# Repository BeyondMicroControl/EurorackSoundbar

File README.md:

# Eurorack Soundbar
Goal: A table with fitting speaker & synth electronics for a MIDI keyboard.

# Piano enclosures deserve better design
It all started with buying an all-in-one furnished hammer-action piano with built-in synth and speakers, but ending 25 years later with a shell containing a terribly old synth and procrastinating MIDI interface.  That said, while build quality on all parts of the piano gracefull survived decades of playing, electronics inside turned out to be fashion-sensitive. As a matter of fact, furniture built-in synths sooner or later all become **OBSOLETE**. I long thought about flinging out the guts out of my good old Clavinova from Yamaha built around a synth chip from 1991 (YMW258-F), but selling my old piano in its original state and figure out a more future-proof enclosure sounded like a better idea, as I really wanted an enclosure allowing more flexibility.  So, here's the plan: 
* Buy a multi-sensor MIDI keyboard - I fell for a KAWAI VPC1, but any model will do.
* Design a slim, good-looking table on wheels carrying about 30Kg=66lbs of keyboard and another 20Kg=44lbs of soundbar.
* Design a soundbar including a standardised built-in rack space for replacable electronics : **A Eurorack Soundbar as it were!**

# Eurorack Soundbar Requirements
## Furniture
1.1) Elegant & aesthetically matching the MIDI keyboard<br>
1.2) Providing table surface fitting Piano Keyboard + Soundbar.<br>
1.3) Sturdy enough to bear stress and strain caused by ~50Kg=110lbs of weight<br>
1.4) Providing maximum leg space horizontally and vertically.<br>
1.5) Height-adjustable to some extent.<br>
1.6) Piano-black glossy paint finish.<br>

## Speaker enclosure - passive part
2.1) Perfectly fitting keyboard width, and height aligned with the top of the speaker grills.<br>
2.2) Best compromise between good bass production and small enclosure volume.<br>
2.3) Rich sound spectrum and spatial perception ideal for instrument sound reproduction.<br>
2.4) Optional built-in passive filter and accessble attenuators whenever necessary.<br>
2.5) Die-cast, anti-reflection and airleak-proof speaker enclosure.<br>
2.6) Vibration isolation between table & enclosure.<br>
2.7) Does not vibrate or glide off the table.<br>
2.8) Re-openable, allowing replacement of speakers provided with inside fixture.<br>
2.9) All speaker leads and filter leads come straight out of the pressure cabinet. (No electrical circuits inside)<br>
2.10) One common connector (male part) providing electrically separate access to all enclosed speakers and filters.<br>
2.11) Nicely fitting speaker cover frame wrapped in speaker cover fabric, with magnetic attachment<br>
2.12) Speakers pointing upwards, providing a fairly unobstructed sound path<br>

## Electronics enclosure - active part
3.1) One common connector (female part, heading towards the amplifier) with configurable dispatching jumpers.<br>
3.2) Standard Eurorack frame housing 3U 84HP (decisive for speaker enclosure depth).<br>
3.3) Eurorack power source (Low noise 15-35V source for Amps, 5V & 3V3 regulated source for MCU's and controllers), optionally with a 1-button on/off and power-on sequence.<br>
3.4) A good compromise on the divide between Eurorack enclosure height (located between bottom plate and face plate) and speaker enclosure duct height (located under the Eurorack bottom plate).<br>
3.6) Mains inlet connector with fast fuse and manual switch.<br>
3.5) At least 3 essential Eurorack modules<br>
   - Amp (2 x 30-80W)
   - Piano connector face plate (USB-midi, MIDI-in/out)
   - Synth module (MIDI-in to audio)

3.6) Optional Eurorack modules - just brainstorming<br>
   - Battery module providing mobile power
   - Additional experimental synths (without patch cable clutter)
   - MIDI merger/splitter module
   - MIDI controller module (encoders, buttons, sliders, tone wheels, LEDs, touchscreens...)
   - MIDI sequencer / tempo

# Getting sketchy with it

This is the initial sketch, for what it's worth, outlining all elements including the Piano; we'll come back later on the exact measures and additional features; obviously depending on the MIDI keyboard outer dimensions one has purchased.  

This is our first step, planning how this soundbar will fit best fit behind your MIDI keyboard, the outer dimensions of the table, how your knees will ideally fit under that table, and many other practical considerations.

# Hardware

<a href="https://beyondmicrocontrol.github.io/AsciiCAD/index.html?d=eNrdm8tu20YUhvd+ilnGCFhrqKuXjuykaiwJlWTBgCADXXhbA21gpF3FWnURBBRAOUQgo6mq9IIYSBduFwXaRR+gD8En6eFlyBnORSQtiZMKY1miyNGZ75w55+eIrD6vonbrsIVanb3uyQD14Omoh7b3eNI5RK59xbYP3Jb0bSPH7qCiHw+rQ+D0wm+35MWEvEjTbtm3mY5NdCI9tnhOwQNMDJ+4rYLt4bbgD4ZxBRt24dWTL56dJ0bkzmx3ZnHtNdefeD/5AbKBqPpJ14k7/SkxZtd+KQ+ErHFhidk1hzurjXdnU3jeg90v3Nl7plPkvvoraoTFFI1qHVxujMMj04z++jvYd/QZxmMY9qAD30NNqhEu/fP747Eqisjjggsg72hyuGvbFL2IIaEBs9fDMWXJh63v2RR+Mnt/Af/2IjauPYf3I9Ms/fvrmKCBzxYPOs1dhIbNpjv7PsVsl3tPFHPTs7OzcI/rv+F5wHqHb7+49ttc+URtGuOAB7QD5pIvv6Wovn4himzeN9gkzpnE/rm+C170yNAdEnN0tFphpnn1Z9QS1s0Ww8cPvcOGR+ApNg8lIlyUl1Bk2ITM2x4bw6uz4FztpQvqjcPa4b0a4U61gevjYIbPk/Sgfu+wNtqUjYIJfkd5gXjr+g+qZyeaC4DO8NF1JUEe9zKq1KkZoiZp06FNu3g70W3R1YlkoAfiVP+zIG3SgxOmXoME9OXlJR3N7CzmM43fFbi7giuNwN0kzYCTfQ/cckQc8QSYqFxgi1Mgm4/kqTnqHfAw6Tmcn56iDEclQLVDCkLJKwj2IA7UUR82JeqQg4TmUh/P3ijr/I1nJAylMk4kLXVukuRn5bfdsEAUOSHpm5AmVNcTjI7rjeOxlN4qE6Q23qTNV7yZ4lDKrskU47fjbN0NNw5bJOk4PIXNakJ3+jYNh9XyKqpmMNkhvGtjf4okZJWazaqoEzqYipatKkAFrWja12gdGEU+YwMUE1JLblOn9ck9zqrW0mgDLN3UZmDWUhLHK/QmKfMJcxMVR1Ij7BSxu8y4XRbOcTmeaKAo1blDoiqDg+yQNYpZM91KWE+Zb/gtMPik/4hY/oFTAxJmegjJ5Up8K6TkUp1cJpJaLyEqLX8CijpIPyE0tfijKvGquS4SCzSv0eD8/Muvv0GVT0pjNa+oNJi8IjQ1UoSWgGgaPbhCkaXhedBro+bFV8/OnxvtOqqVSu1Pv1XF35Y1ovyEI7VKSxlVGWbhpjXiD+k4ZFaJ9bEk4we9v1wdrLNFeA4mewxbHSoROxroRQG5KC3UMynGZdQxzD4OVxJU7xQj1OydmnCQURL9OsJVLIcqlRrqO3EMrkvhscl3ooY78OEOAriYg1seliXD9aXF9J1WGk7CdQ0qjpneEwTDWPjbuycDnxw8mWUDtZvHT7EXq0DyYB/MvtBVr6lQrVWx8SZZAo7HPSBnIqMMHE0jtKfpB+dBI+JYvGKTYluXZvNqlr+2EZfWJKtHPipkVIAVNvy3GPVO+54GqUuCwYoVXJlXcGUtFJwlobs2/cYh5dm2Ot50RkYV2JZIHA4CtjXlRGNpb1vfxX8Jt10hhHe3vsJCv75jNYwwh2KQQkYNTN0H5v3mManyB1Vv7jOD3opuXIj5CqcEEDaLInyn3IEXUmZA+wBo14F2w6N9eBDRrohpF6Q4lSkIqJeLoi74scqW6yvTyyq+sjIawLweMMeQVSoe83KKrGLpLGclpzuRmyqFu8lSyTfcBMfsg2NqQerxSqnvGJMDY7F1RCPpqzjtBA9UC/QAU9TZWT1btD/v91Cz74/PwCWEq6Tk9k7Lng8w5QOLl2F6imupQ8AVtW26Yglnb4xFURh5E6Dd7bdCiQ3wMcKVWO/48EvU2CdytaaFMpdwB+J1j7h/aWDetS6GHluSgGKr30UQx8c+RRNhOAsMzv/6zadwXnN06NdUsZ3UumqFV+UVLVS5Q9tL0ALXxm5U4bOunjXUq2fsOUCulUVN1lpJaoo/Ju5u5Fwv4+C8yfLz233ajQLwpuX4j2rE0SUd/qt1LqRNUi2bI4WE5UKx4MVbdiz3XxyL+50X97O+LB2KPaCniJbVWWVLLNgxHzFLdtT+6j2FUs6i3s6LvoYji8u1XJ0WTME1rR7SE3GisZ8E3tJ9nTzptHUtSoouitfZaYKfIzValldX6lySP+edNYy4r/LivqrRRROOMMIzivr9LKI+H8/tCXlZkXMSNwkRB+/nkPPTpa9sqcXmvFhy3wE2XbJ9zaXBt9ErEYsYOwXhXda7SrJf/1foCMPb2/Le65H/596PpTlrA43y3c+R4ZK+ewfVBse5vgvt9B1lPk2hs9ey1XlcGm8g2W10jNHtraVMVdrR3XH3rsNI+xHmrb8fycjuV3n/N83Ru/ZqWjH/AyNxXoU=">Input module</a>

# Tools

<a href=https://beyondmicrocontrol.github.io/EurorackSoundbar/tools/TOOLS_CATALOG.html>TOOLS</a>

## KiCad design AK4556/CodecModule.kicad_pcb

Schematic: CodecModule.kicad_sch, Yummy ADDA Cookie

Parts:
C1, C3, C4, C5: 10u; CP_Elec_4x5.4
C2, C6, C9: 100n; C_0603_1608Metric_Pad1.05x0.95mm_HandSolder
C7, C8: 22u; CP_Elec_4x5.4
C10: 2u2; CP_Elec_4x5.4
J1, J2: Conn_01x09_Female; HalfHole_2x9
R3: 5R1; R_0603_1608Metric_Pad1.05x0.95mm_HandSolder
R4, R5, R6, R7, R8: 51R; R_0603_1608Metric_Pad1.05x0.95mm_HandSolder
R9, R10, R11: 10k; R_0603_1608Metric_Pad1.05x0.95mm_HandSolder
R12, R13: 220R; R_0603_1608Metric_Pad1.05x0.95mm_HandSolder
U1: AK4556; TSSOP-20_4.4x6.5mm_P0.65mm

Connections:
+3.3VA: C5.1, C6.1, J1.4, R3.2, U1.4, U1.6
/AUDIO_INL: C4.1, J1.1
/AUDIO_INR: C3.1, J1.2
/AUDIO_OUTL: J2.9, R13.1
/AUDIO_OUTR: J2.8, R12.1
/CKS0: J1.5, U1.9
/CKS1: J1.6, U1.10
/CKS2: J1.7, U1.11
/CKS3: J1.8, U1.12
/I2S_BCLK: J2.6, R5.1
/I2S_DIN: J2.2, R8.1
/I2S_DOUT: J2.1, R4.2
/I2S_LRCLK: J2.4, R7.1
/I2S_MCLK: J2.5, R6.1
/PDN: J1.9, R11.2, U1.17
/VD: C1.1, C2.1, R3.1, U1.5
GNDA: C1.2, C2.2, C5.2, C6.2, C9.2, C10.2, J1.3, J2.3, J2.7, R9.1, R10.1, R11.1, U1.3, U1.7
unnamed: C3.2, U1.1
unnamed: C4.2, U1.2
unnamed: C7.1, U1.20
unnamed: C7.2, R9.2, R12.2
unnamed: C8.1, U1.19
unnamed: C8.2, R10.2, R13.2
unnamed: C9.1, C10.1, U1.18
unnamed: R4.1, U1.8
unnamed: R5.2, U1.16
unnamed: R6.2, U1.15
unnamed: R7.2, U1.14
unnamed: R8.2, U1.13

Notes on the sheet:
place near VD/VSS pin
De-emphasis filter off

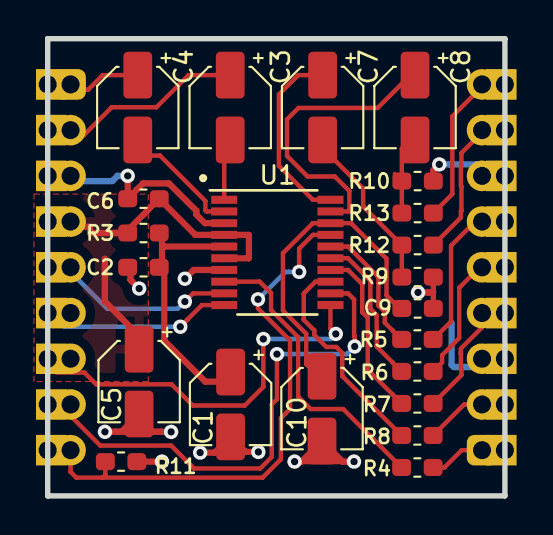
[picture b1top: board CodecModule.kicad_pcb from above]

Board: 2 copper layers, 25.4 x 25.4 mm, 24 parts (0 on the bottom side), 29 nets.

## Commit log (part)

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2026-01-08 Fix typo in project title in README
2026-01-08 Fix image source URL in menu generation
2026-01-08 no longer needed
2026-01-08 input module v0
2026-01-08 bitmapper
2026-01-08 AsciiCAD
2026-01-08 AsciiCAD helper tools
2026-01-08 Teensy
2026-01-15 cleanup
2026-01-27 audio2midi - test
2026-02-06 moved AsciiCAD into a separate project
2026-02-06 adding a few tools
